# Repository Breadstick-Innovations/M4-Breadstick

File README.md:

# M4-Breadstick(retired) → [Raspberry Breadstick](https://github.com/Breadstick-Innovations/Raspberry-Breadstick)

## [Raspberry Breadstick Crowd Supply Campaign](https://www.crowdsupply.com/breadstick-innovations/raspberry-breadstick)
Be sure to [Subscribe!](https://www.crowdsupply.com/breadstick-innovations/raspberry-breadstick)

## [Hackaday IO](https://hackaday.io/project/180819-m4-breadstick)

## Adafruit Attribution
The M4-Breadstick is an adaptation of Adafruit's ItsyBitsy M4 Express; details about their board can be found [here](https://github.com/adafruit/Adafruit-ItsyBitsy-M4-Express-PCB).

## Design
### Goal
* Adapt a modern development board to a form factor which better compliments breadboard prototyping by reducing the number, length, and crossing of jumper-wires.

<insert more about the design shape and potential use cases>

### Examples
* Blink
  * [Files](Examples/1.%20Blink)
  * [YouTube Video](https://www.youtube.com/watch?v=jlcFvwoJDTA&list=PLvRCEIc8WROOZ6hJWuxPTIbie-fAAK2j3)

* Buttons
  * [Files](Examples/7.%20Many%20Buttons)
  * [YouTube Video](https://www.youtube.com/watch?v=LMG715chEnE&list=PLvRCEIc8WROOZ6hJWuxPTIbie-fAAK2j3&index=6)

* Potentiometers
  * [Files](Examples/3.%20Potentiometer/)
  * [YouTube Video](https://www.youtube.com/watch?v=UZgDf5CVg4E&list=PLvRCEIc8WROOZ6hJWuxPTIbie-fAAK2j3&index=3)

* Dual I2C Display
  * [Files](Examples/5.%20Dual%20I2C%20Display/)
  * [YouTube Video](https://www.youtube.com/watch?v=ZbwT2mgDPAQ&list=PLvRCEIc8WROOZ6hJWuxPTIbie-fAAK2j3&index=5)

* 24 Adressable RGB LED Strip (Dot-Star Compatible)
  * [Files](Examples/2.%20LED%20Strip)
  * [YouTube Video](https://www.youtube.com/watch?v=AKLR_5SblVk&list=PLvRCEIc8WROOZ6hJWuxPTIbie-fAAK2j3&index=2)

* Motor Driver Demo
  * [Files](Examples/8.%20Motor%20Driver)
  * [YouTube Video](https://www.youtube.com/watch?v=vfRkdXOv09Y&list=PLvRCEIc8WROOZ6hJWuxPTIbie-fAAK2j3&index=7)

## Adafruit ItsyBitsy M4 Express PCB

<a href="http://www.adafruit.com/products/3800"><br/>
Click here to purchase one from the Adafruit shop</a>

PCB files for the Adafruit ItsyBitsy M4 Express. PCB format is EagleCAD schematic and board layout

For more details, check out the product pages at
* https://www.adafruit.com/products/3800

### Description

What's smaller than a Feather but larger than a Trinket? It's an Adafruit ItsyBitsy M4 Express featuring the Microchip ATSAMD51! Small, powerful, with a ultra fast ATSAMD51 Cortex M4 processor running at 120 MHz - this microcontroller board is perfect when you want something very compact, with a ton of horsepower and a bunch of pins. This Itsy is like a bullet train, with it's 120MHz Cortex M4 with floating point support and 512KB Flash and 192KB RAM. Your code will zig and zag and zoom, and with a bunch of extra peripherals for support, this will for sure be your favorite new chipset.

ItsyBitsy M4 Express is only 1.4" long by 0.7" wide, but has 6 power pins, 23 digital GPIO pins (7 of which can be analog in, 2 x 1 MSPS analog out DACs, and 18 x PWM out). It's the same chip as the Adafruit Metro M4 but really really small. So it's great once you've finished up a prototype on a Metro M4 or (the upcoming) Feather M4, and want to make the project much smaller. It even comes with 2MB of SPI Flash built in, for data logging, file storage, or CircuitPython code.

The most exciting part of the ItsyBitsy M4 is that while you can use it with the Arduino IDE, we are shipping it with CircuitPython on board. When you plug it in, it will show up as a very small disk drive with main.py on it. Edit main.py with your favorite text editor to build your project using Python, the most popular programming language. No installs, IDE or compiler needed, so you can use it on any computer, even ChromeBooks or computers you can't install software on. When you're done, unplug the Itsy' and your code will go with you.

### License

Adafruit invests time and resources providing this open source design, please support Adafruit and open-source hardware by purchasing products from [Adafruit](https://www.adafruit.com)!

Designed by Limor Fried/Ladyada for Adafruit Industries.

Creative Commons Attribution/Share-Alike, all text above must be included in any redistribution. See license.txt for additional details.

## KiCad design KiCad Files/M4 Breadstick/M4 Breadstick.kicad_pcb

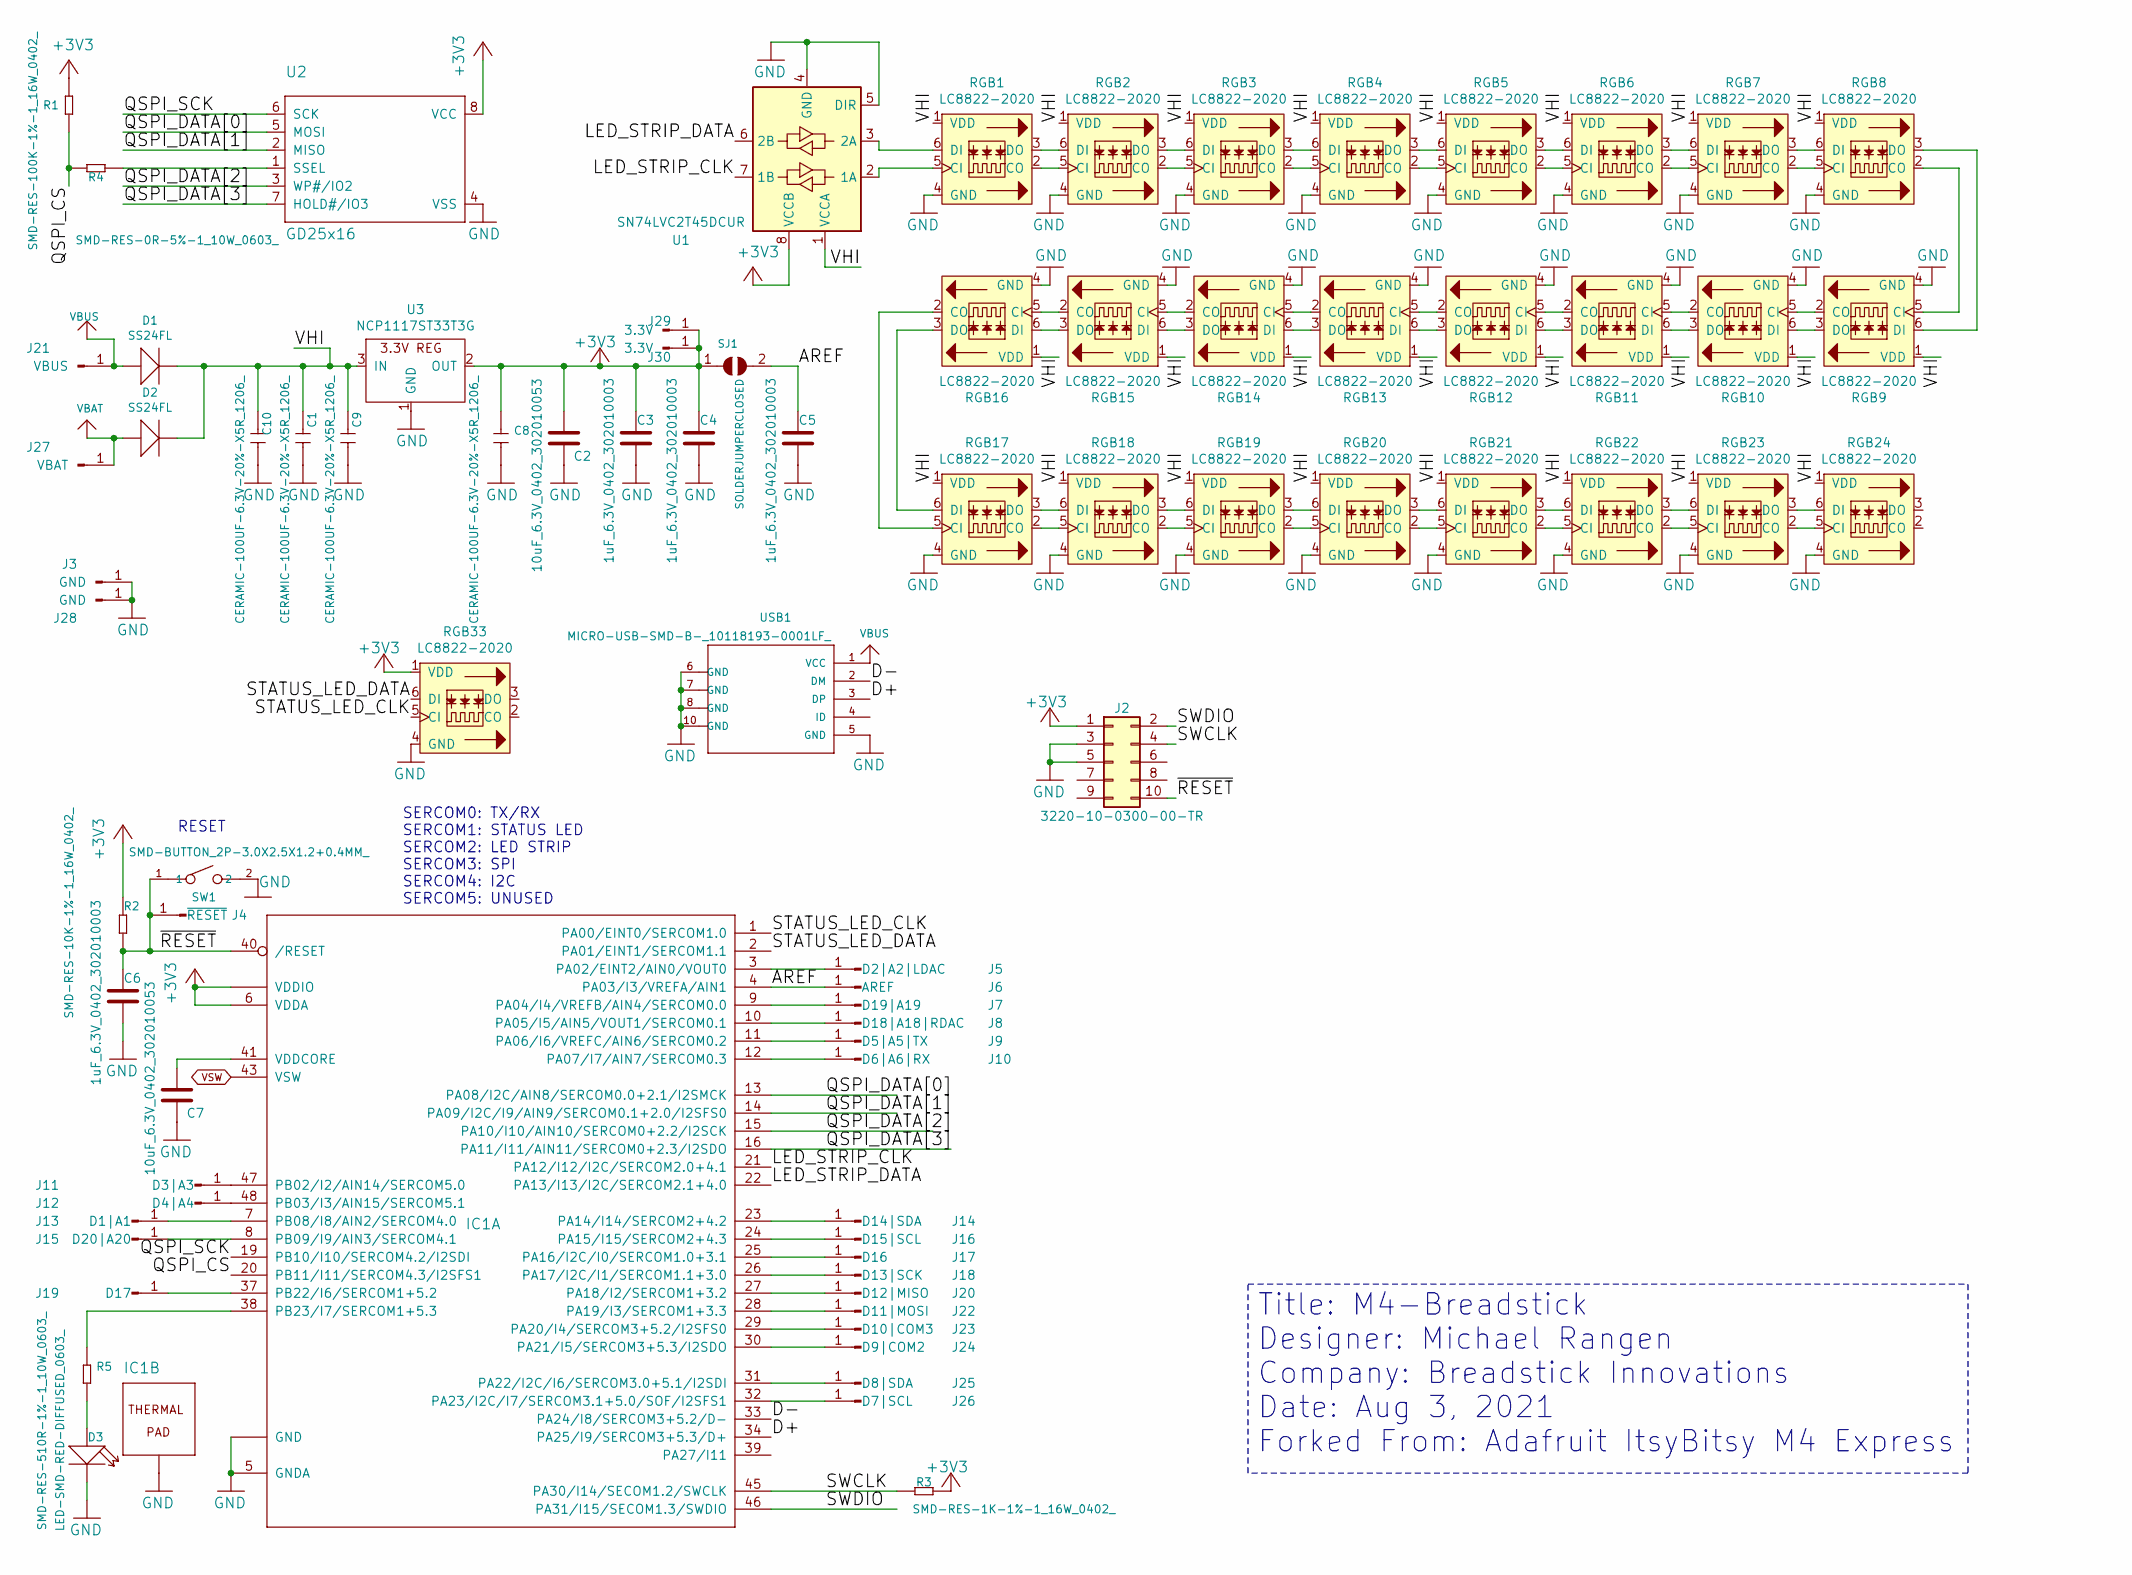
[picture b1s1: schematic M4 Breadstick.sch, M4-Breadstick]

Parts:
C1, C8, C9, C10: CERAMIC-100UF-6.3V-20%-X5R_1206_; C1206; MPN GRM31CR60J107ME39L
C2, C7: 10uF_6.3V_0402_302010053; C0402
C3, C4, C5, C6: 1uF_6.3V_0402_302010003; C0402
D1, D2: SS24FL; SOD-123; MPN B5819W
D3: LED-SMD-RED-DIFFUSED_0603_; LED-0603; MPN 19-217-R6C-AL1M2VY-3T
IC1: ATSAMD51G_TQFN48; TQFN48_7MM
J2: 3220-10-0300-00-TR; SWD_02x05_1.27mm_SMT
J3, J28: GND; Pin_Header_Straight_1x01_Pitch2.54mm
J4: ~RESET; Pin_Header_Straight_1x01_Pitch2.54mm
J5: D2|A2|LDAC; Pin_Header_Straight_1x01_Pitch2.54mm
J6: AREF; Pin_Header_Straight_1x01_Pitch2.54mm
J7: D19|A19; Pin_Header_Straight_1x01_Pitch2.54mm
J8: D18|A18|RDAC; Pin_Header_Straight_1x01_Pitch2.54mm
J9: D5|A5|TX; Pin_Header_Straight_1x01_Pitch2.54mm
J10: D6|A6|RX; Pin_Header_Straight_1x01_Pitch2.54mm
J11: D3|A3; Pin_Header_Straight_1x01_Pitch2.54mm
J12: D4|A4; Pin_Header_Straight_1x01_Pitch2.54mm
J13: D1|A1; Pin_Header_Straight_1x01_Pitch2.54mm
J14: D14|SDA; Pin_Header_Straight_1x01_Pitch2.54mm
J15: D20|A20; Pin_Header_Straight_1x01_Pitch2.54mm
J16: D15|SCL; Pin_Header_Straight_1x01_Pitch2.54mm
J17: D16; Pin_Header_Straight_1x01_Pitch2.54mm
J18: D13|SCK; Pin_Header_Straight_1x01_Pitch2.54mm
J19: D17; Pin_Header_Straight_1x01_Pitch2.54mm
J20: D12|MISO; Pin_Header_Straight_1x01_Pitch2.54mm
J21: VBUS; Pin_Header_Straight_1x01_Pitch2.54mm
J22: D11|MOSI; Pin_Header_Straight_1x01_Pitch2.54mm
J23: D10|COM3; Pin_Header_Straight_1x01_Pitch2.54mm
J24: D9|COM2; Pin_Header_Straight_1x01_Pitch2.54mm
J25: D8|SDA; Pin_Header_Straight_1x01_Pitch2.54mm
J26: D7|SCL; Pin_Header_Straight_1x01_Pitch2.54mm
J27: VBAT; Pin_Header_Straight_1x01_Pitch2.54mm
J29, J30: 3.3V; Pin_Header_Straight_1x01_Pitch2.54mm
R1: SMD-RES-100K-1%-1_16W_0402_; R0402; MPN RC0402FR-07100KL
R2: SMD-RES-10K-1%-1_16W_0402_; R0402; MPN RC0402FR-0710KL
R3: SMD-RES-1K-1%-1_16W_0402_; R0402; MPN RC0603JR-072K2L
R4: SMD-RES-0R-5%-1_10W_0603_; R0603; MPN RC0603JR-070RL
R5: SMD-RES-510R-1%-1_10W_0603_; R0603; MPN RC0603FR-07510RL
RGB1, RGB2, RGB3, RGB4, RGB5, RGB6, RGB7, RGB8, RGB9, RGB10, RGB11, RGB12, RGB13, RGB14, RGB15, RGB16, RGB17, RGB18, RGB19, RGB20, RGB21, RGB22, RGB23, RGB24, RGB33: LC8822-2020
SJ1: SOLDERJUMPERCLOSED; SOLDERJUMPER_CLOSEDWIRE
SW1: SMD-BUTTON_2P-3.0X2.5X1.2+0.4MM_; SW2-2.6-3.0X2.5X1.2+0.4MM; MPN B3U-1000P-2P-SMD
U1: SN74LVC2T45DCUR; VSSOP-8_2.3x2mm_Pitch0.5mm
U2: GD25x16; USON8
U3: NCP1117ST33T3G; SOT-223
USB1: MICRO-USB-SMD-B-_10118193-0001LF_; MICRO-USB5+6P-SMD-0.65-B; MPN 10118193-0001LF

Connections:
+3V3: C2.1, C3.1, C4.1, C8.1, IC1.6 (VDDA), IC1.17 (VDDIO), IC1.36 (VDDIO), IC1.44 (VDDIO), J2.1, J29.1, J30.1, R1.1, R2.2, R3.2, RGB33.1 (VDD), SJ1.1, U1.8 (VCCB), U2.8 (VCC), U3.2 (OUT)
/AREF: C5.1, IC1.4 (PA03/I3/VREFA/AIN1), J6.1, SJ1.2
/D+: IC1.34 (PA25/I9/SERCOM3+5.3/D+), USB1.3 (DP)
/D-: IC1.33 (PA24/I8/SERCOM3+5.2/D-), USB1.2 (DM)
/LED_STRIP_CLK: IC1.21 (PA12/I12/I2C/SERCOM2.0+4.1), U1.7 (1B)
/LED_STRIP_DATA: IC1.22 (PA13/I13/I2C/SERCOM2.1+4.0), U1.6 (2B)
/QSPI_CS: IC1.20 (PB11/I11/SERCOM4.3/I2SFS1), R1.2, R4.1
/QSPI_DATA[0]: IC1.13 (PA08/I2C/AIN8/SERCOM0.0+2.1/I2SMCK), U2.5 (MOSI)
/QSPI_DATA[1]: IC1.14 (PA09/I2C/I9/AIN9/SERCOM0.1+2.0/I2SFS0), U2.2 (MISO)
/QSPI_DATA[2]: IC1.15 (PA10/I10/AIN10/SERCOM0+2.2/I2SCK), U2.3 (WP#/IO2)
/QSPI_DATA[3]: IC1.16 (PA11/I11/AIN11/SERCOM0+2.3/I2SDO), U2.7 (HOLD#/IO3)
/QSPI_SCK: IC1.19 (PB10/I10/SERCOM4.2/I2SDI), U2.6 (SCK)
/STATUS_LED_CLK: IC1.1 (PA00/EINT0/SERCOM1.0), RGB33.5 (CI)
/STATUS_LED_DATA: IC1.2 (PA01/EINT1/SERCOM1.1), RGB33.6 (DI)
/SWCLK: IC1.45 (PA30/I14/SECOM1.2/SWCLK), J2.4, R3.1
/SWDIO: IC1.46 (PA31/I15/SECOM1.3/SWDIO), J2.2
/VHI: C1.1, C9.1, C10.1, D1.2 (-), D2.2 (-), RGB1.1 (VDD), RGB2.1 (VDD), RGB3.1 (VDD), RGB4.1 (VDD), RGB5.1 (VDD), RGB6.1 (VDD), RGB7.1 (VDD), RGB8.1 (VDD), RGB9.1 (VDD), RGB10.1 (VDD), RGB11.1 (VDD), RGB12.1 (VDD), RGB13.1 (VDD), RGB14.1 (VDD), RGB15.1 (VDD), RGB16.1 (VDD), RGB17.1 (VDD), RGB18.1 (VDD), RGB19.1 (VDD), RGB20.1 (VDD), RGB21.1 (VDD), RGB22.1 (VDD), RGB23.1 (VDD), RGB24.1 (VDD), U1.1 (VCCA), U3.3 (IN)
/~RESET: C6.1, IC1.40 (/RESET), J2.10, J4.1, R2.1, SW1.1
GND: C1.2, C2.2, C3.2, C4.2, C5.2, C6.2, C7.2, C8.2, C9.2, C10.2, D3.2 (-), IC1.5 (GNDA), IC1.18 (GND), IC1.35 (GND), IC1.42 (GND), IC1.THERMAL (TP), J2.3, J2.5, J3.1, J28.1, RGB1.4 (GND), RGB2.4 (GND), RGB3.4 (GND), RGB4.4 (GND), RGB5.4 (GND), RGB6.4 (GND), RGB7.4 (GND), RGB8.4 (GND), RGB9.4 (GND), RGB10.4 (GND), RGB11.4 (GND), RGB12.4 (GND), RGB13.4 (GND), RGB14.4 (GND), RGB15.4 (GND), RGB16.4 (GND), RGB17.4 (GND), RGB18.4 (GND), RGB19.4 (GND), RGB20.4 (GND), RGB21.4 (GND), RGB22.4 (GND), RGB23.4 (GND), RGB24.4 (GND), RGB33.4 (GND), SW1.2, U1.4 (GND), U1.5 (DIR), U2.4 (VSS), U3.1 (GND), USB1.5 (GND), USB1.6 (GND), USB1.7 (GND), USB1.8 (GND), USB1.9 (GND), USB1.10 (GND), USB1.11 (GND)
unnamed: C7.1, IC1.41 (VDDCORE)
unnamed: D3.1 (+), R5.2
unnamed: IC1.3 (PA02/EINT2/AIN0/VOUT0), J5.1
unnamed: IC1.7 (PB08/I8/AIN2/SERCOM4.0), J13.1
unnamed: IC1.8 (PB09/I9/AIN3/SERCOM4.1), J15.1
unnamed: IC1.9 (PA04/I4/VREFB/AIN4/SERCOM0.0), J7.1
unnamed: IC1.10 (PA05/I5/AIN5/VOUT1/SERCOM0.1), J8.1
unnamed: IC1.11 (PA06/I6/VREFC/AIN6/SERCOM0.2), J9.1
unnamed: IC1.12 (PA07/I7/AIN7/SERCOM0.3), J10.1
unnamed: IC1.23 (PA14/I14/SERCOM2+4.2), J14.1
unnamed: IC1.24 (PA15/I15/SERCOM2+4.3), J16.1
unnamed: IC1.25 (PA16/I2C/I0/SERCOM1.0+3.1), J17.1
unnamed: IC1.26 (PA17/I2C/I1/SERCOM1.1+3.0), J18.1
unnamed: IC1.27 (PA18/I2/SERCOM1+3.2), J20.1
unnamed: IC1.28 (PA19/I3/SERCOM1+3.3), J22.1
unnamed: IC1.29 (PA20/I4/SERCOM3+5.2/I2SFS0), J23.1
unnamed: IC1.30 (PA21/I5/SERCOM3+5.3/I2SDO), J24.1
unnamed: IC1.31 (PA22/I2C/I6/SERCOM3.0+5.1/I2SDI), J25.1
unnamed: IC1.32 (PA23/I2C/I7/SERCOM3.1+5.0/SOF/I2SFS1), J26.1
unnamed: IC1.37 (PB22/I6/SERCOM1+5.2), J19.1
unnamed: IC1.38 (PB23/I7/SERCOM1+5.3), R5.1
unnamed: IC1.47 (PB02/I2/AIN14/SERCOM5.0), J11.1
unnamed: IC1.48 (PB03/I3/AIN15/SERCOM5.1), J12.1
unnamed: R4.2, U2.1 (SSEL)
unnamed: RGB1.2 (CO), RGB2.5 (CI)
unnamed: RGB1.3 (DO), RGB2.6 (DI)
unnamed: RGB1.5 (CI), U1.2 (1A)
unnamed: RGB1.6 (DI), U1.3 (2A)
unnamed: RGB2.2 (CO), RGB3.5 (CI)
unnamed: RGB2.3 (DO), RGB3.6 (DI)
unnamed: RGB3.2 (CO), RGB4.5 (CI)
unnamed: RGB3.3 (DO), RGB4.6 (DI)
unnamed: RGB4.2 (CO), RGB5.5 (CI)
unnamed: RGB4.3 (DO), RGB5.6 (DI)
unnamed: RGB5.2 (CO), RGB6.5 (CI)
unnamed: RGB5.3 (DO), RGB6.6 (DI)
unnamed: RGB6.2 (CO), RGB7.5 (CI)
unnamed: RGB6.3 (DO), RGB7.6 (DI)
unnamed: RGB7.2 (CO), RGB8.5 (CI)
unnamed: RGB7.3 (DO), RGB8.6 (DI)
unnamed: RGB8.2 (CO), RGB9.5 (CI)
unnamed: RGB8.3 (DO), RGB9.6 (DI)
unnamed: RGB10.2 (CO), RGB11.5 (CI)
unnamed: RGB10.3 (DO), RGB11.6 (DI)
unnamed: RGB9.2 (CO), RGB10.5 (CI)
unnamed: RGB9.3 (DO), RGB10.6 (DI)
unnamed: RGB11.2 (CO), RGB12.5 (CI)
unnamed: RGB11.3 (DO), RGB12.6 (DI)
unnamed: RGB12.2 (CO), RGB13.5 (CI)
unnamed: RGB12.3 (DO), RGB13.6 (DI)
unnamed: RGB13.2 (CO), RGB14.5 (CI)
unnamed: RGB13.3 (DO), RGB14.6 (DI)
unnamed: RGB14.2 (CO), RGB15.5 (CI)
unnamed: RGB14.3 (DO), RGB15.6 (DI)
unnamed: RGB15.2 (CO), RGB16.5 (CI)
unnamed: RGB15.3 (DO), RGB16.6 (DI)
unnamed: RGB16.2 (CO), RGB17.5 (CI)
unnamed: RGB16.3 (DO), RGB17.6 (DI)
unnamed: RGB17.2 (CO), RGB18.5 (CI)
unnamed: RGB17.3 (DO), RGB18.6 (DI)
unnamed: RGB18.2 (CO), RGB19.5 (CI)
unnamed: RGB18.3 (DO), RGB19.6 (DI)
unnamed: RGB19.2 (CO), RGB20.5 (CI)
unnamed: RGB19.3 (DO), RGB20.6 (DI)
unnamed: RGB20.2 (CO), RGB21.5 (CI)
unnamed: RGB20.3 (DO), RGB21.6 (DI)
unnamed: RGB21.2 (CO), RGB22.5 (CI)
unnamed: RGB21.3 (DO), RGB22.6 (DI)
unnamed: RGB22.2 (CO), RGB23.5 (CI)
unnamed: RGB22.3 (DO), RGB23.6 (DI)
unnamed: RGB23.2 (CO), RGB24.5 (CI)
unnamed: RGB23.3 (DO), RGB24.6 (DI)
VBAT: D2.1 (+), J27.1
VBUS: D1.1 (+), J21.1, USB1.1 (VCC)
VSW: IC1.43 (VSW)

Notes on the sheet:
RESET
SERCOM0: TX/RX SERCOM1: STATUS LED SERCOM2: LED STRIP SERCOM3: SPI SERCOM4: I2C SERCOM5: UNUSED
Title: M4-Breadstick Designer: Michael Rangen Company: Breadstick Innovations Date: Aug 3, 2021 Forked From: Adafruit ItsyBitsy M4 Express

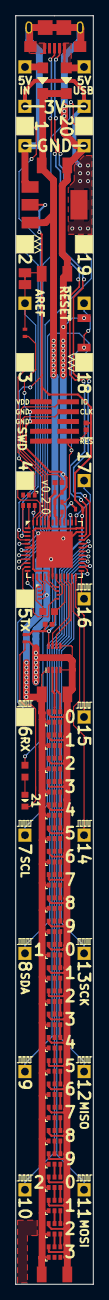
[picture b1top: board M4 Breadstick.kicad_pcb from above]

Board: 4 copper layers, 10.0 x 163.6 mm, 79 parts (0 on the bottom side), 93 nets.

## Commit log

2021-08-09 Cleared ItsyBitsy M4-Express Files
2021-08-09 Returned Photo Of ItsyBitsy M4 Express
2021-08-09 Changed Asset folder to Adafruit Assets
2021-08-09 Fix Readme Link To Image
2021-08-09 Example Folder Upload
2021-08-09 Try to get image working...
2021-08-09 Converted some images from HEIC to JPG
2021-08-09 Fixed Rotated Image
    The JPG was not rotated properly. Rotating, saving, and pushing did not fix. Created a properly rotated PNG and that image worked.
2021-08-09 Added README files to examples
2021-08-09 Moved videos to YouTube
2021-08-09 Added Design Files and Documentation
2021-08-10 Update README.md
    added Adafuit ItsyBitsy reference back in.
2021-11-07 Multi sheets created
2021-11-07 LEDs moved to child sheet
2021-11-07 page template done
    needs review from mike
